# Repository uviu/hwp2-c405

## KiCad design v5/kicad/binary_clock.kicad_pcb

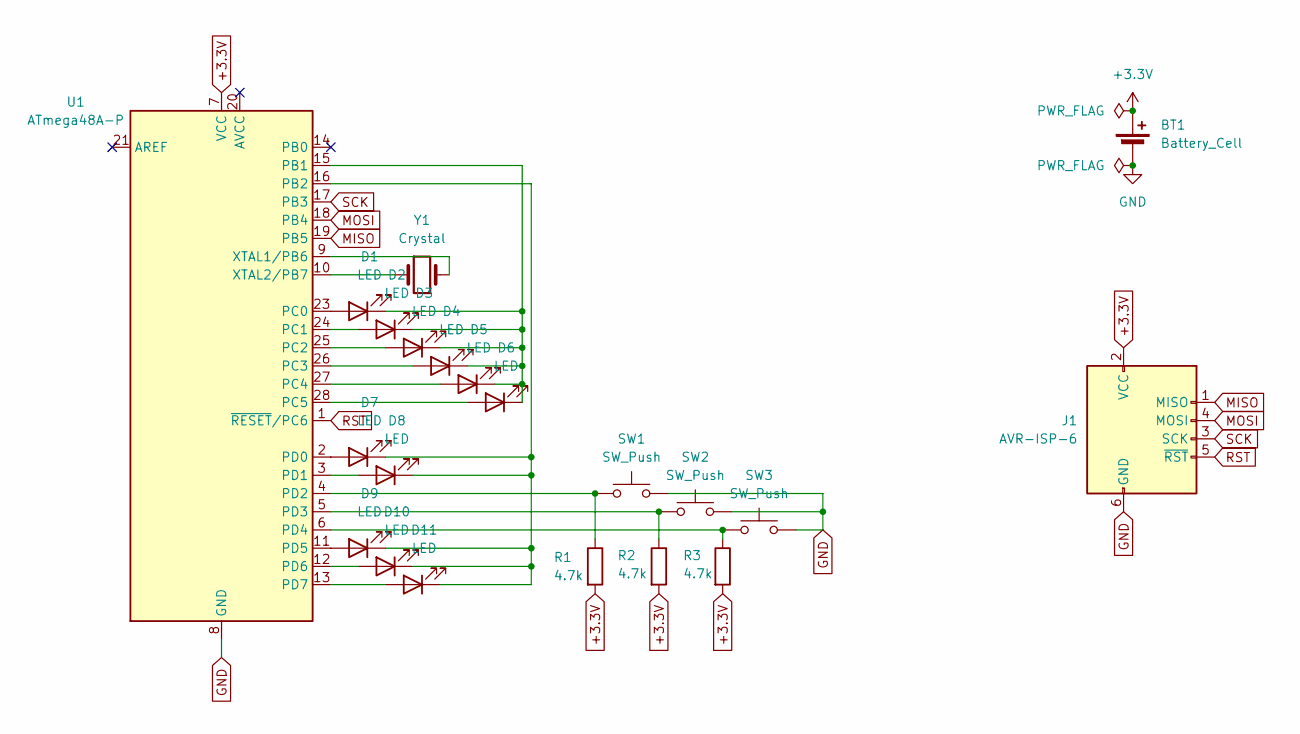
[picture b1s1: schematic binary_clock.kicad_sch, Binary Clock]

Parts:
BT1: Battery_Cell; BatteryHolder_Keystone_103_1x20mm
D1, D2, D3, D4, D5, D6, D7, D8, D9, D10, D11: LED; LED_D3.0mm
J1: AVR-ISP-6; PinSocket_2x03_P2.54mm_Vertical
R1, R2, R3: 4.7k; R_Axial_DIN0207_L6.3mm_D2.5mm_P10.16mm_Horizontal
SW1, SW2, SW3: SW_Push; SW_PUSH_6mm
U1: ATmega48A-P; DIP-28_W7.62mm
Y1: Crystal; Crystal_DS10_D1.0mm_L4.3mm_Vertical

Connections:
+3.3V: BT1.1 (+), J1.2 (VCC), R1.2, R2.2, R3.2, U1.7 (VCC)
GND: BT1.2 (-), J1.6 (GND), SW1.2, SW2.2, SW3.2, U1.8 (GND), U1.22 (GND)
MISO: J1.1 (MISO), U1.19 (PB5)
MOSI: J1.4 (MOSI), U1.18 (PB4)
unnamed: D1.2 (A), U1.23 (PC0)
unnamed: D1.1 (K), D2.1 (K), D3.1 (K), D4.1 (K), D5.1 (K), D6.1 (K), U1.15 (PB1)
unnamed: D2.2 (A), U1.24 (PC1)
unnamed: D3.2 (A), U1.25 (PC2)
unnamed: D4.2 (A), U1.26 (PC3)
unnamed: D5.2 (A), U1.27 (PC4)
unnamed: D6.2 (A), U1.28 (PC5)
unnamed: D7.2 (A), U1.2 (PD0)
unnamed: D8.2 (A), U1.3 (PD1)
unnamed: D9.2 (A), U1.11 (PD5)
unnamed: D10.2 (A), U1.12 (PD6)
unnamed: D7.1 (K), D8.1 (K), D9.1 (K), D10.1 (K), D11.1 (K), U1.16 (PB2)
unnamed: D11.2 (A), U1.13 (PD7)
unnamed: R1.1, SW1.1, U1.4 (PD2)
unnamed: R2.1, SW2.1, U1.5 (PD3)
unnamed: R3.1, SW3.1, U1.6 (PD4)
unnamed: U1.9 (XTAL1/PB6), Y1.2
unnamed: U1.10 (XTAL2/PB7), Y1.1
RST: J1.5 (~RST), U1.1 (~RESET/PC6)
SCK: J1.3 (SCK), U1.17 (PB3)

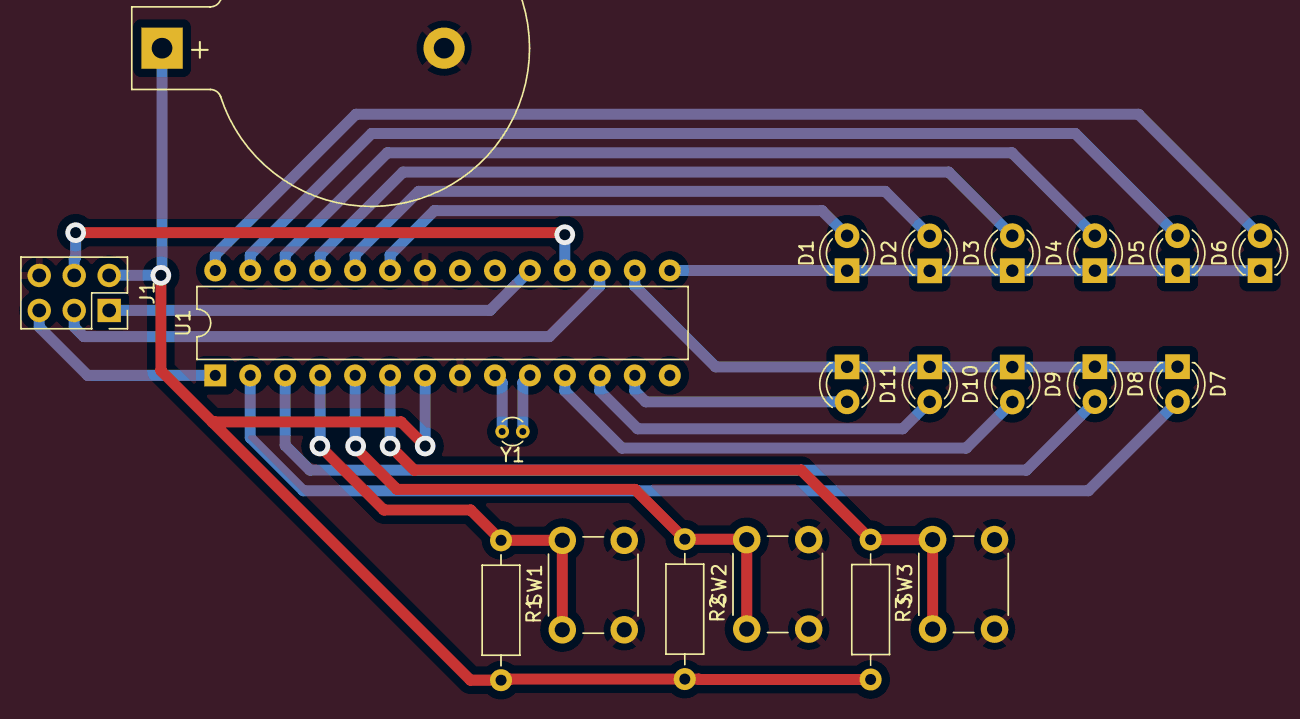
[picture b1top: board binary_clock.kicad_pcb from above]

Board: 2 copper layers, 21 parts (0 on the bottom side), 24 nets.

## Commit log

2024-11-27 Rename hwp7.pdf to v7/hwp7.pdf
2024-11-29 Rename v7/b15f.cpp to v7/src/b15f.cpp
2024-11-29 fixed inputfile path
2024-12-01 Rename b15f.cpp to encode.cpp
    more appropriate name
2024-12-04 fixed encoding
2024-12-05 decode ohne crc Überprüfung reingeknallt
2024-12-05 Code aufgeräumt
2024-12-05 Update arduinoReceive.py
    analog gepusht
2024-12-05 fixed clock offset
2024-12-05 fixed output file
2024-12-05 bin dir
2024-12-05 Rename encode to encode
2024-12-05 Rename send to send
2024-12-06 read instead of readline
2024-12-06 erstelle recieveFiebertraum
2024-12-12 Rename binary_clock.kicad_pcb to v5/kicad/binary_clock.kicad_pcb
2024-12-12 Rename binary_clock.kicad_pro to v5/kicad/binary_clock.kicad_pro
2024-12-12 Rename binary_clock.kicad_sch to v5/kicad/binary_clock.kicad_sch
2025-01-14 Rename v7/src/completeReceive.cpp to v7/src/receive/completeReceive.cpp
2025-01-14 Rename v7/src/compareFiles.cpp to v7/src/receive/compareFiles.cpp
2025-01-14 Rename v7/src/stringToBinary.cpp to v7/src/receive/stringToBinary.cpp
2025-01-14 Rename v7/src/decode.cpp to v7/src/receive/decode.cpp
2025-01-14 Rename v7/src/encode.cpp to v7/src/send/encode.cpp
